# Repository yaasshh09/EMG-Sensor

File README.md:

## System Overview

The MyoRead is an EMG sensor made up of a four-stage analog circuit that picks up the tiny electrical signals your muscles give off when they contract and cleans them up enough for a computer to read. It's built around the cheap, everyday LM358P op-amp to keep costs down.

```
Forearm electrodes 
      |
      v
[Stage 1] Instrumentation Amplifier   -- 101x gain, rejects common-mode noise
      |
      v
[Stage 2] Twin-T 50 Hz Notch Filter   -- kills UAE mains hum
      |
      v
[Stage 3] Sallen-Key Bandpass 20-500 Hz -- isolates EMG band
      |
      v
[Stage 4] Half-wave rectifier + RC envelope (tau = 47 ms)
```

## Signal Chain

All op-amp stages use the **LM358P** (DIP-8, single supply 5 V).

The LM358P output swings only 0.05 V to 3.5 V on a 5 V supply. A 2.5 V DC bias is applied at every stage input so the AC signal can swing symmetrically without clipping.

### Stage 0 -- Bias circuit

Two matched 10 kohm resistors from 5 V to GND. Midpoint = 2.5 V.

```
V_bias = 5V x R2 / (R1 + R2) = 5V x 10k / 20k = 2.5 V
```

### Stage 1 - 3-op-amp instrumentation amplifier

```
Gain = 1 + (2 x Rf / Rg) = 1 + (2 x 100k / 2k) = 101x
```

- Rf = 100 kohm x2 (feedback around OA1, OA2)
- Rg = 2 kohm (single resistor between OA1 IN- and OA2 IN-)
- OA3 difference amplifier: 4 matched 10 kohm resistors

CMRR depends on matching the four OA3 resistors. Select four from the kit using a multimeter: target within 1% of each other.

### Stage 2 - Twin-T 50 Hz notch filter

```
f_notch = 1 / (2pi x R x C)
R = 1 / (2pi x 50 x 100nF) = 31.8 kohm --> 33 kohm (E24 standard)
Centre resistor: R/2 = 15 kohm
Centre capacitor: 2C = 220 nF
Actual f_notch with 33 kohm: 48.2 Hz -- effective against 50 Hz hum
```

Followed by a unity-gain op-amp buffer to restore drive capability.

### Stage 3 - Sallen-Key bandpass 20-500 Hz

High-pass (20 Hz):
```
C = 100 nF
R = 1 / (2pi x 20 x 100nF) = 79.6 kohm --> 82 kohm
Actual cutoff: 19.4 Hz
```

Low-pass (500 Hz):
```
C = 10 nF
R = 1 / (2pi x 500 x 10nF) = 31.8 kohm --> 33 kohm
Actual cutoff: 482 Hz
```

### Stage 4 - Envelope detector

```
Half-wave rectifier: 1N4148 signal diode (stripe = cathode, faces output)
RC smoother: R = 4.7 kohm, C = 10 uF electrolytic
tau = R x C = 4700 x 0.00001 = 47 ms

Constraint: 1/500Hz = 2ms << tau << 1/20Hz = 50ms  (satisfied)
```

The output is a slowly-varying DC voltage proportional to muscle activation level. This feeds directly into your  microcontroller.

## Electrode placement

```
FOREARM (palm facing up, elbow left, wrist right)

+------------------------------------------+
|  ELBOW <----------------------- WRIST    |
|                                          |
|  [IN+]  [IN-]                   [REF]    |
|  2-3 cm apart, over muscle belly  bony   |
|  (inner forearm, palm side)       bump   |
+------------------------------------------+
```

- IN+ and IN- over the forearm flexor muscle belly, 2-3 cm apart along the muscle fibre direction
- REF on the bony wrist prominence (styloid process) -- no muscle underneath, picks up noise only

Skin prep: alcohol wipe, apply conductive gel under each pad. Target skin impedance below 10 kohm between electrodes.

## Bill Of Materials

| Component | Manufacturer Part Number | Description | Quantity | Unit Price | Total Price |
|-----------|--------------------------|-------------|---------:|-----------:|------------:|
| 10 kΩ Resistor | MFR-25FRF52-10K | RES 10K OHM 1% 1/4W AXIAL | 10 | $0.042 | $0.42 |
| 33 kΩ Resistor | MFR-25FTE52-33K | RES 33K OHM 1% 1/4W AXIAL | 10 | $0.042 | $0.42 |
| 1 MΩ Resistor | MFR-25FRF52-1M | RES 1M OHM 1% 1/4W AXIAL | 2 | $0.100 | $0.20 |
| 100 kΩ Resistor | MFR-25FBF52-100K | RES 100K OHM 1% 1/4W AXIAL | 2 | $0.100 | $0.20 |
| 82 kΩ Resistor | MFR-25FBF52-82K | RES 82K OHM 1% 1/4W AXIAL | 2 | $0.100 | $0.20 |
| 15 kΩ Resistor | MFR-25FBF52-15K | RES 15K OHM 1% 1/4W AXIAL | 1 | $0.100 | $0.10 |
| 4.7 kΩ Resistor | MFR-25FTE52-4K7 | RES 4.7K OHM 1% 1/4W AXIAL | 1 | $0.100 | $0.10 |
| 22 kΩ Resistor | MFR-25FTE52-22K | RES 22K OHM 1% 1/4W AXIAL | 1 | $0.100 | $0.10 |
| Signal Diode | 1N4148 | DIODE STANDARD 100V 200MA DO35 | 1 | $0.100 | $0.10 |
| Operational Amplifier | LM358P | IC OPAMP GP 2 CIRCUIT 8DIP | 3 | $0.330 | $0.99 |
| 2 kΩ Resistor | MFR-25FBF52-2K | RES 2K OHM 1% 1/4W AXIAL | 1 | $0.100 | $0.10 |
| 100 nF Ceramic Capacitor | K104K15X7RF5TL2 | CAP CER 0.1UF 50V X7R RADIAL | 10 | $0.167 | $1.67 |
| 10 nF Ceramic Capacitor | A103K15X7RF5TAA | CAP CER 10000PF 50V X7R AXIAL | 2 | $0.260 | $0.52 |
| 10 µF Electrolytic Capacitor | 50YXJ10M5X11 | CAP ALUM 10UF 20% 50V RADIAL TH | 2 | $0.320 | $0.64 |
| 220 nF Ceramic Capacitor | FG14X7R1H224KNT00 | CAP CER 0.22UF 50V X7R RADIAL | 1 | $0.280 | $0.28 |

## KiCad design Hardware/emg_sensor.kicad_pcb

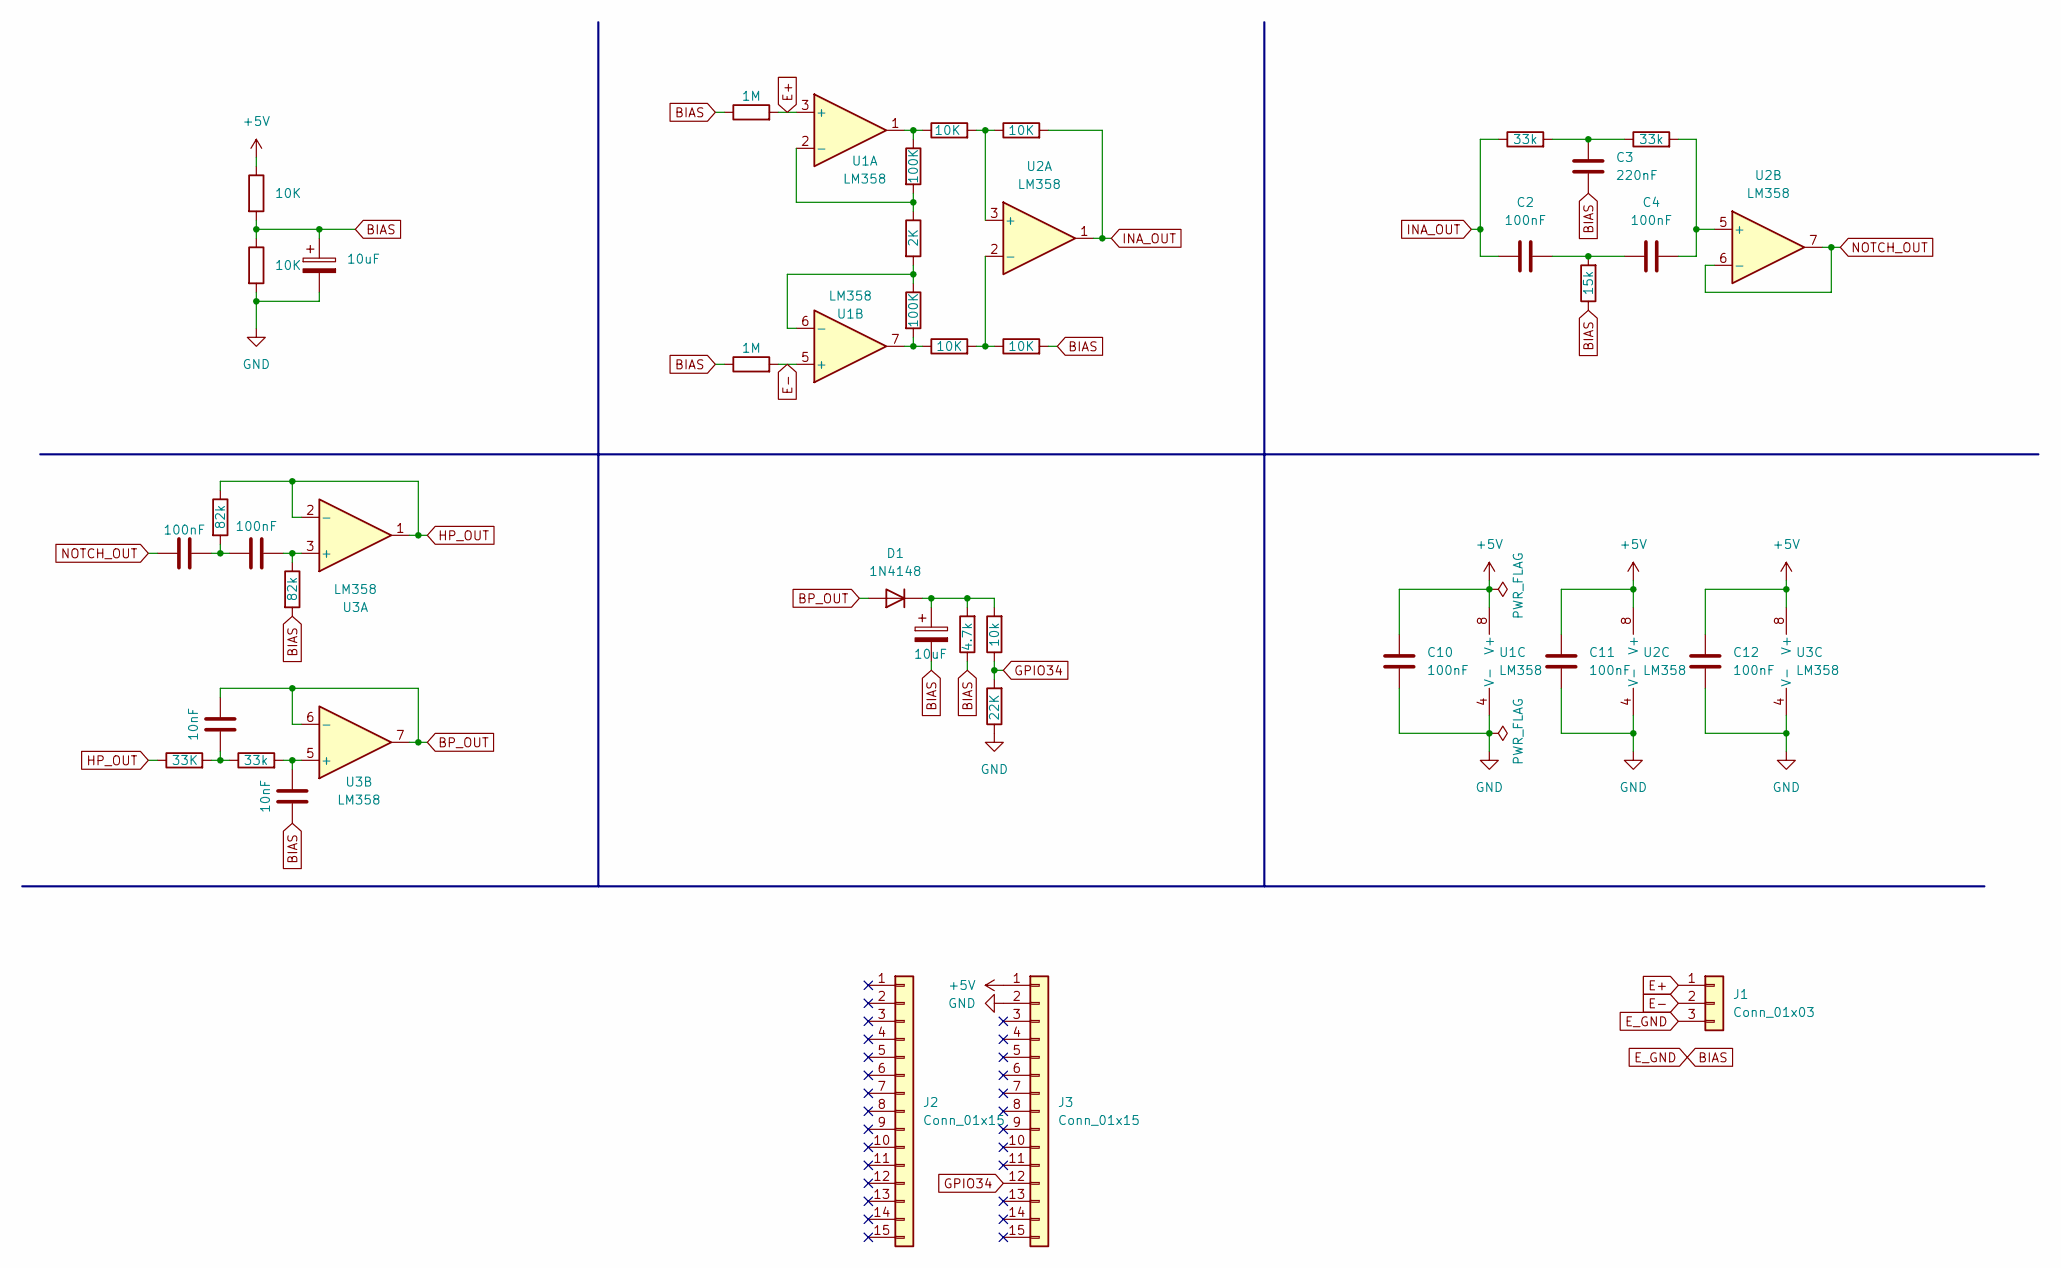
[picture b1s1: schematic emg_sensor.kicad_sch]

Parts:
C1, C9: 10uF; CP_Radial_D5.0mm_P2.00mm
C2, C4, C5, C7, C10, C11, C12: 100nF; C_Disc_D5.0mm_W2.5mm_P2.50mm
C3: 220nF; C_Disc_D5.0mm_W2.5mm_P2.50mm
C6, C8: 10nF; C_Disc_D5.0mm_W2.5mm_P2.50mm
D1: 1N4148; D_DO-35_SOD27_P7.62mm_Horizontal
J1: Conn_01x03; SolderWire-0.5sqmm_1x03_P4.6mm_D0.9mm_OD2.1mm
J2, J3: Conn_01x15; PinHeader_1x15_P2.54mm_Vertical
R1, R2, R7, R8, R9, R10: 10K; R_Axial_DIN0207_L6.3mm_D2.5mm_P10.16mm_Horizontal
R3, R4: 1M; R_Axial_DIN0207_L6.3mm_D2.5mm_P10.16mm_Horizontal
R5, R6: 100K; R_Axial_DIN0207_L6.3mm_D2.5mm_P10.16mm_Horizontal
R11, R13, R16: 33k; R_Axial_DIN0207_L6.3mm_D2.5mm_P10.16mm_Horizontal
R12: 15k; R_Axial_DIN0207_L6.3mm_D2.5mm_P10.16mm_Horizontal
R14: 33K; R_Axial_DIN0207_L6.3mm_D2.5mm_P10.16mm_Horizontal
R15, R17: 82k; R_Axial_DIN0207_L6.3mm_D2.5mm_P10.16mm_Horizontal
R18: 4.7k; R_Axial_DIN0207_L6.3mm_D2.5mm_P10.16mm_Horizontal
R19: 10k; R_Axial_DIN0207_L6.3mm_D2.5mm_P10.16mm_Horizontal
R20: 22K; R_Axial_DIN0207_L6.3mm_D2.5mm_P10.16mm_Horizontal
Rgain1: 2K; R_Axial_DIN0207_L6.3mm_D2.5mm_P10.16mm_Horizontal
U1, U2, U3: LM358; DIP-8_W7.62mm

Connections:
+5V: C10.1, C11.1, C12.1, J3.1, R1.1, U1.8 (V+), U2.8 (V+), U3.8 (V+)
BIAS: C1.1, C3.2, C8.1, C9.2, J1.3, R1.2, R2.1, R3.1, R4.1, R10.2, R12.1, R17.2, R18.1
BP_OUT: C6.2, D1.2 (A), U3.6 (-), U3.7
E+: J1.1, R3.2, U1.3 (+)
E-: J1.2, R4.2, U1.5 (+)
GND: C1.2, C10.2, C11.2, C12.2, J3.2, R2.2, R20.1, U1.4 (V-), U2.4 (V-), U3.4 (V-)
GPIO34: J3.12, R19.1, R20.2
HP_OUT: R14.1, R15.1, U3.1, U3.2 (-)
INA_OUT: C2.1, R9.2, R11.1, U2.1
NOTCH_OUT: C5.1, U2.6 (-), U2.7
unnamed: C2.2, C4.1, R12.2
unnamed: C3.1, R11.2, R13.1
unnamed: C5.2, C7.1, R15.2
unnamed: C6.1, R14.2, R16.1
unnamed: C9.1, D1.1 (K), R18.2, R19.2
unnamed: R5.1, R7.1, U1.1
unnamed: R6.2, R8.1, U1.7
unnamed: R5.2, Rgain1.1, U1.2 (-)
unnamed: R6.1, Rgain1.2, U1.6 (-)
unnamed: R7.2, R9.1, U2.3 (+)
unnamed: R8.2, R10.1, U2.2 (-)
unnamed: C4.2, R13.2, U2.5 (+)
unnamed: C7.2, R17.1, U3.3 (+)
unnamed: C8.2, R16.2, U3.5 (+)

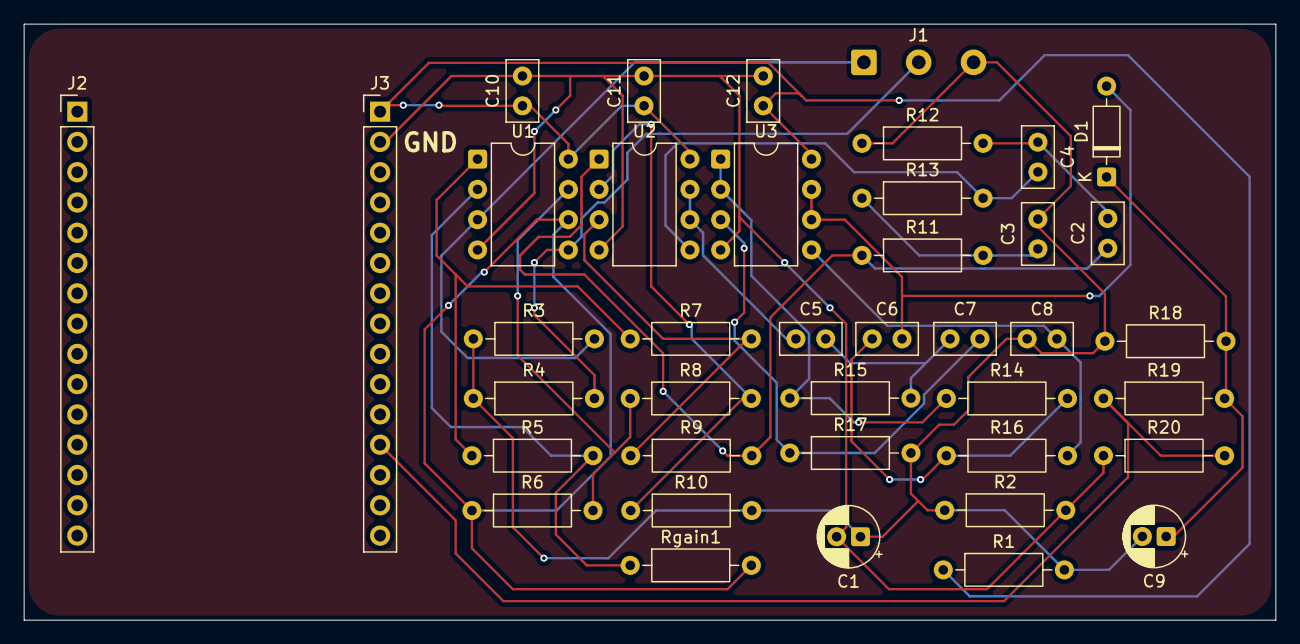
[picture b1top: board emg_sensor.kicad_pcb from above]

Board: 2 copper layers, 105.0 x 50.0 mm, 40 parts (0 on the bottom side), 24 nets.

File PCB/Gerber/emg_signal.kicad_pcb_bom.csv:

Designator,Quantity,Value,Footprint,Package,MPN,DNP,Mount_Type,Description,KiLib_Generator,Sim.Device,Sim.Pins
"C1, C9",2,10uF,CP_Radial_D5.0mm_P2.00mm,,,,tht,Polarized capacitor,capacitor/THT/other,,
"C10, C11, C12, C2, C4, C5, C7",7,100nF,C_Disc_D5.0mm_W2.5mm_P2.50mm,,,,tht,Unpolarized capacitor,capacitor/THT/other,,
C3,1,220nF,C_Disc_D5.0mm_W2.5mm_P2.50mm,,,,tht,Unpolarized capacitor,capacitor/THT/other,,
"C6, C8",2,10nF,C_Disc_D5.0mm_W2.5mm_P2.50mm,,,,tht,Unpolarized capacitor,capacitor/THT/other,,
D1,1,1N4148,D_DO-35_SOD27_P7.62mm_Horizontal,,,,tht,"100V 0.15A standard switching diode, DO-35",diode/THT,D,1=K 2=A
J1,1,Conn_01x03,SolderWire-0.5sqmm_1x03_P4.6mm_D0.9mm_OD2.1mm,,,,tht,"Generic connector, single row, 01x03, script generated (kicad-library-utils/schlib/autogen/connector/)",connector/wire,,
"J2, J3",2,Conn_01x15,PinHeader_1x15_P2.54mm_Vertical,,,,tht,"Generic connector, single row, 01x15, script generated (kicad-library-utils/schlib/autogen/connector/)",connector/pin_header_socket,,
"R1, R10, R2, R7, R8, R9",6,10K,R_Axial_DIN0207_L6.3mm_D2.5mm_P10.16mm_Horizontal,,,,tht,Resistor,resistor/THT,,
"R11, R13, R16",3,33k,R_Axial_DIN0207_L6.3mm_D2.5mm_P10.16mm_Horizontal,,,,tht,Resistor,resistor/THT,,
R12,1,15k,R_Axial_DIN0207_L6.3mm_D2.5mm_P10.16mm_Horizontal,,,,tht,Resistor,resistor/THT,,
R14,1,33K,R_Axial_DIN0207_L6.3mm_D2.5mm_P10.16mm_Horizontal,,,,tht,Resistor,resistor/THT,,
"R15, R17",2,82k,R_Axial_DIN0207_L6.3mm_D2.5mm_P10.16mm_Horizontal,,,,tht,Resistor,resistor/THT,,
R18,1,4.7k,R_Axial_DIN0207_L6.3mm_D2.5mm_P10.16mm_Horizontal,,,,tht,Resistor,resistor/THT,,
R19,1,10k,R_Axial_DIN0207_L6.3mm_D2.5mm_P10.16mm_Horizontal,,,,tht,Resistor,resistor/THT,,
R20,1,22K,R_Axial_DIN0207_L6.3mm_D2.5mm_P10.16mm_Horizontal,,,,tht,Resistor,resistor/THT,,
"R3, R4",2,1M,R_Axial_DIN0207_L6.3mm_D2.5mm_P10.16mm_Horizontal,,,,tht,Resistor,resistor/THT,,
"R5, R6",2,100K,R_Axial_DIN0207_L6.3mm_D2.5mm_P10.16mm_Horizontal,,,,tht,Resistor,resistor/THT,,
Rgain1,1,2K,R_Axial_DIN0207_L6.3mm_D2.5mm_P10.16mm_Horizontal,,,,tht,Resistor,resistor/THT,,
"U1, U2, U3",3,LM358,DIP-8_W7.62mm,,,,tht,"Low-Power, Dual Operational Amplifiers, DIP-8/SOIC-8/TO-99-8",package/DIP/legacy,,
